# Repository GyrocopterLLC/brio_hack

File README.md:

# brio_hack

A simple PCB that repairs (and improves!) a circa mid-1990s Brio wooden train electronic light and sound signal crossing. I inherited one. The PCB was completely shot. So I measured the board, made a Kicad design, had it fabbed and reconnected it to the toy.

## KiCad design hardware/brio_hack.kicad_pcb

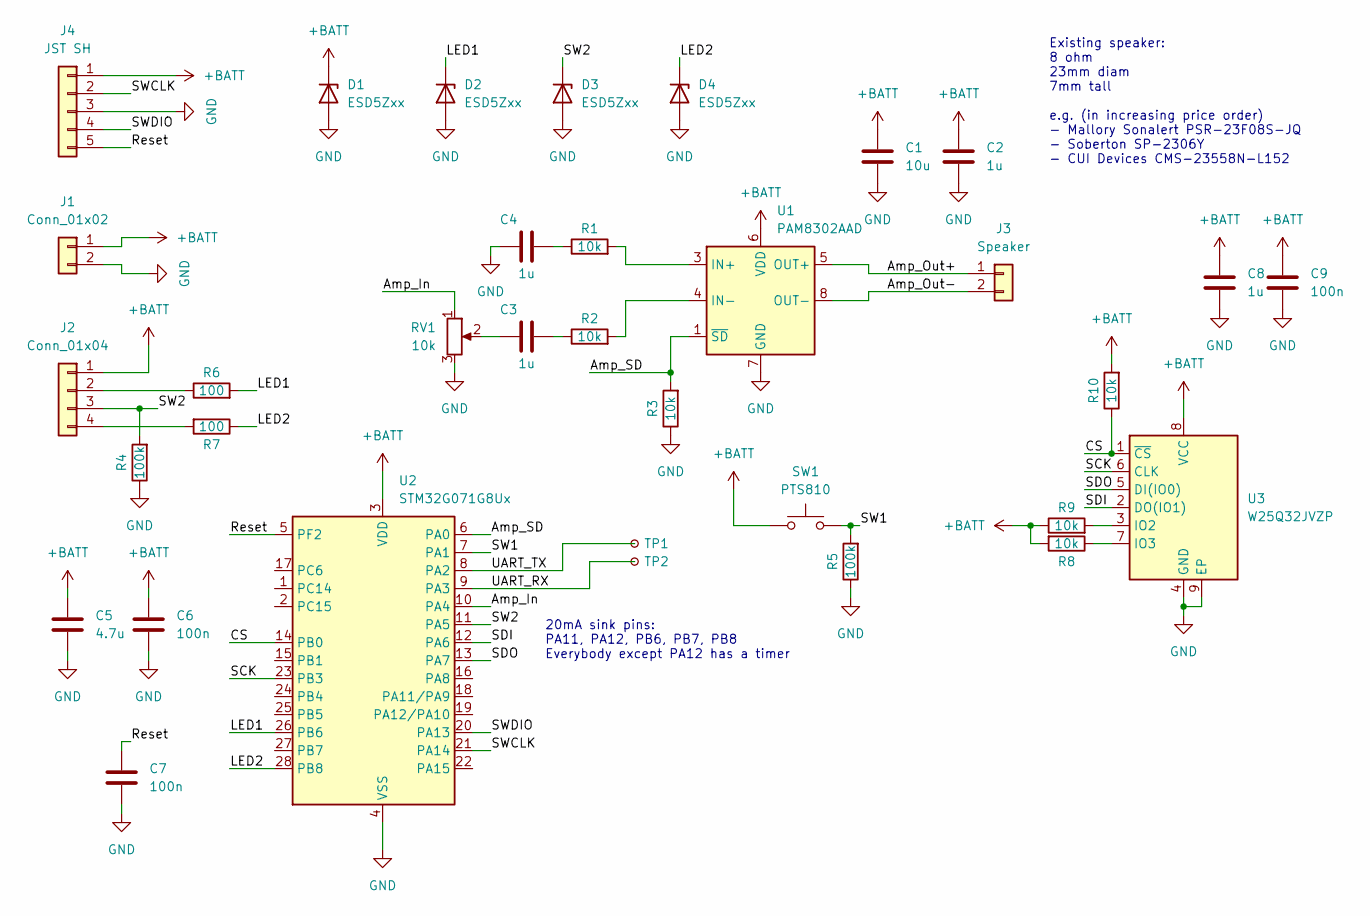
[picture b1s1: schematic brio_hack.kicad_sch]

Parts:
C1: 10u; C_0402_1005Metric
C2, C3, C4, C8: 1u; C_0402_1005Metric
C5: 4.7u; C_0402_1005Metric
C6, C7, C9: 100n; C_0402_1005Metric
D1, D2, D3, D4: ESD5Zxx; D_SOD-523
J1: Conn_01x02; PinHeader_1x02_P1.00mm_Vertical
J2: Conn_01x04; PinHeader_1x04_P1.00mm_Vertical
J3: Speaker; PinHeader_1x02_P1.00mm_Vertical
J4: JST SH; JST_SH_BM05B-SRSS-TB_1x05-1MP_P1.00mm_Vertical
R1, R2, R3, R8, R9, R10: 10k; R_0402_1005Metric
R4, R5: 100k; R_0402_1005Metric
R6, R7: 100; R_0402_1005Metric
RV1: 10k; TC33X2503E
SW1: PTS810; SW_SPST_PTS810
TP1, TP2: TestPoint_Small; TestPoint_Pad_D0.8mm
U1: PAM8302AAD; MSOP-8_3x3mm_P0.65mm
U2: STM32G071G8Ux; QFN-28_4x4mm_P0.5mm
U3: W25Q32JVZP; WSON-8-1EP_6x5mm_P1.27mm_EP3.4x4.3mm

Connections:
+BATT: C1.1, C2.1, C5.1, C6.1, C8.1, C9.1, D1.1 (K), J1.1, J2.1, J4.1, R8.2, R9.1, R10.2, SW1.1, U1.6 (VDD), U2.3 (VDD), U3.8 (VCC)
/Amp_In: RV1.1, U2.10 (PA4)
/Amp_Out+: J3.1, U1.5 (OUT+)
/Amp_Out-: J3.2, U1.8 (OUT-)
/Amp_SD: R3.2, U1.1 (~SD), U2.6 (PA0)
/CS: R10.1, U2.14 (PB0), U3.1 (~CS)
/LED1: D2.1 (K), R6.2, U2.26 (PB6)
/LED2: D4.1 (K), R7.1, U2.28 (PB8)
/Reset: C7.1, J4.5, U2.5 (PF2)
/SCK: U2.23 (PB3), U3.6 (CLK)
/SDI: U2.12 (PA6), U3.2 (DO(IO1))
/SDO: U2.13 (PA7), U3.5 (DI(IO0))
/SW1: R5.2, SW1.2, U2.7 (PA1)
/SW2: D3.1 (K), J2.3, R4.2, U2.11 (PA5)
/SWCLK: J4.2, U2.21 (PA14)
/SWDIO: J4.4, U2.20 (PA13)
/UART_RX: TP2.1, U2.9 (PA3)
/UART_TX: TP1.1, U2.8 (PA2)
GND: C1.2, C2.2, C4.1, C5.2, C6.2, C7.2, C8.2, C9.2, D1.2 (A), D2.2 (A), D3.2 (A), D4.2 (A), J1.2, J4.3, J4.MP, R3.1, R4.1, R5.1, RV1.3, U1.7 (GND), U2.4 (VSS), U3.4 (GND), U3.9 (EP)
unnamed: C3.1, RV1.2
unnamed: C3.2, R2.1
unnamed: C4.2, R1.1
unnamed: J2.2, R6.1
unnamed: J2.4, R7.2
unnamed: R1.2, U1.3 (IN+)
unnamed: R2.2, U1.4 (IN-)
unnamed: R9.2, U3.3 (IO2)
unnamed: R8.1, U3.7 (IO3)

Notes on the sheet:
Existing speaker: 8 ohm 23mm diam 7mm tall e.g. (in increasing price order) - Mallory Sonalert PSR-23F08S-JQ - Soberton SP-2306Y - CUI Devices CMS-23558N-L152
20mA sink pins: PA11, PA12, PB6, PB7, PB8 Everybody except PA12 has a timer

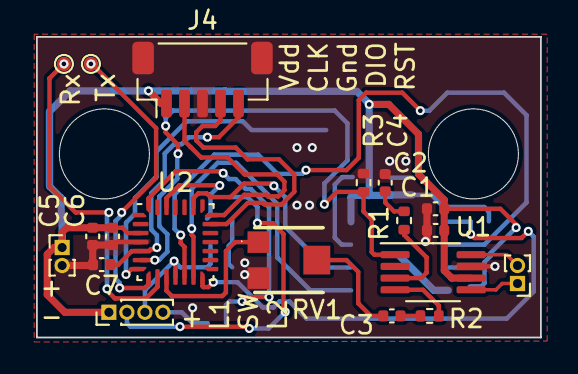
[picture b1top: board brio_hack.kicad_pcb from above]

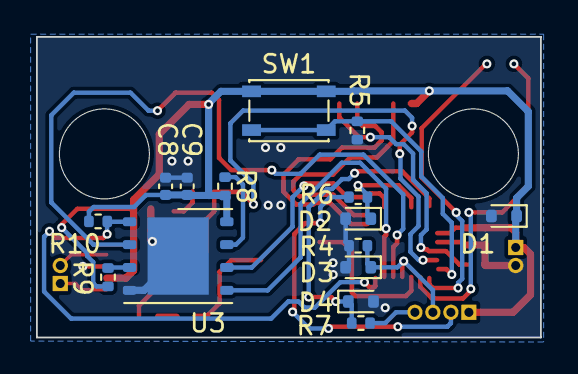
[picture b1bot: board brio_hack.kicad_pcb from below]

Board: 2 copper layers, 28.0 x 16.7 mm, 34 parts (15 on the bottom side), 28 nets.

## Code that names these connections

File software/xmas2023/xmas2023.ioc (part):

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Mcu.Name=STM32G071G(6-8-B)Ux
Mcu.Package=UFQFPN28
Mcu.UserName=STM32G071GBUx
PA0.GPIOParameters=GPIO_Label
PA0.GPIO_Label=Amp_SD
PA0.Signal=GPIO_Output
PA1.GPIOParameters=GPIO_Label,GPIO_ModeDefaultEXTI
PA1.GPIO_Label=SW_Btn
PA1.GPIO_ModeDefaultEXTI=GPIO_MODE_EVT_RISING
PA1.Signal=GPXTI1
PA13.Mode=Serial_Wire
PA13.Signal=SYS_SWDIO
PA14-BOOT0.Mode=Serial_Wire
PA14-BOOT0.Signal=SYS_SWCLK
PA2.Mode=Asynchronous
PA2.Signal=LPUART1_TX
PA3.Mode=Asynchronous
PA3.Signal=LPUART1_RX
PA4.Signal=COMP_DAC11_group
PA5.GPIOParameters=GPIO_Label,GPIO_ModeDefaultEXTI
PA5.GPIO_Label=SW_Reed
PA5.GPIO_ModeDefaultEXTI=GPIO_MODE_EVT_RISING
PA5.Signal=GPXTI5
PA6.Mode=Full_Duplex_Master
PA6.Signal=SPI1_MISO
PA7.Mode=Full_Duplex_Master
PA7.Signal=SPI1_MOSI
PB0.Mode=NSS_Signal_Hard_Output
PB0.Signal=SPI1_NSS
PB3.Mode=Full_Duplex_Master
PB3.Signal=SPI1_SCK
PB6.GPIOParameters=GPIO_Label
PB6.GPIO_Label=LED1
PB6.Signal=S_TIM1_CH3
PB8.GPIOParameters=GPIO_Label
PB8.GPIO_Label=LED2
PB8.Signal=S_TIM16_CH1
RCC.HSE_VALUE=8000000
RCC.SYSCLKFreq_VALUE=64000000
RCC.SYSCLKSource=RCC_SYSCLKSOURCE_PLLCLK
board=custom
